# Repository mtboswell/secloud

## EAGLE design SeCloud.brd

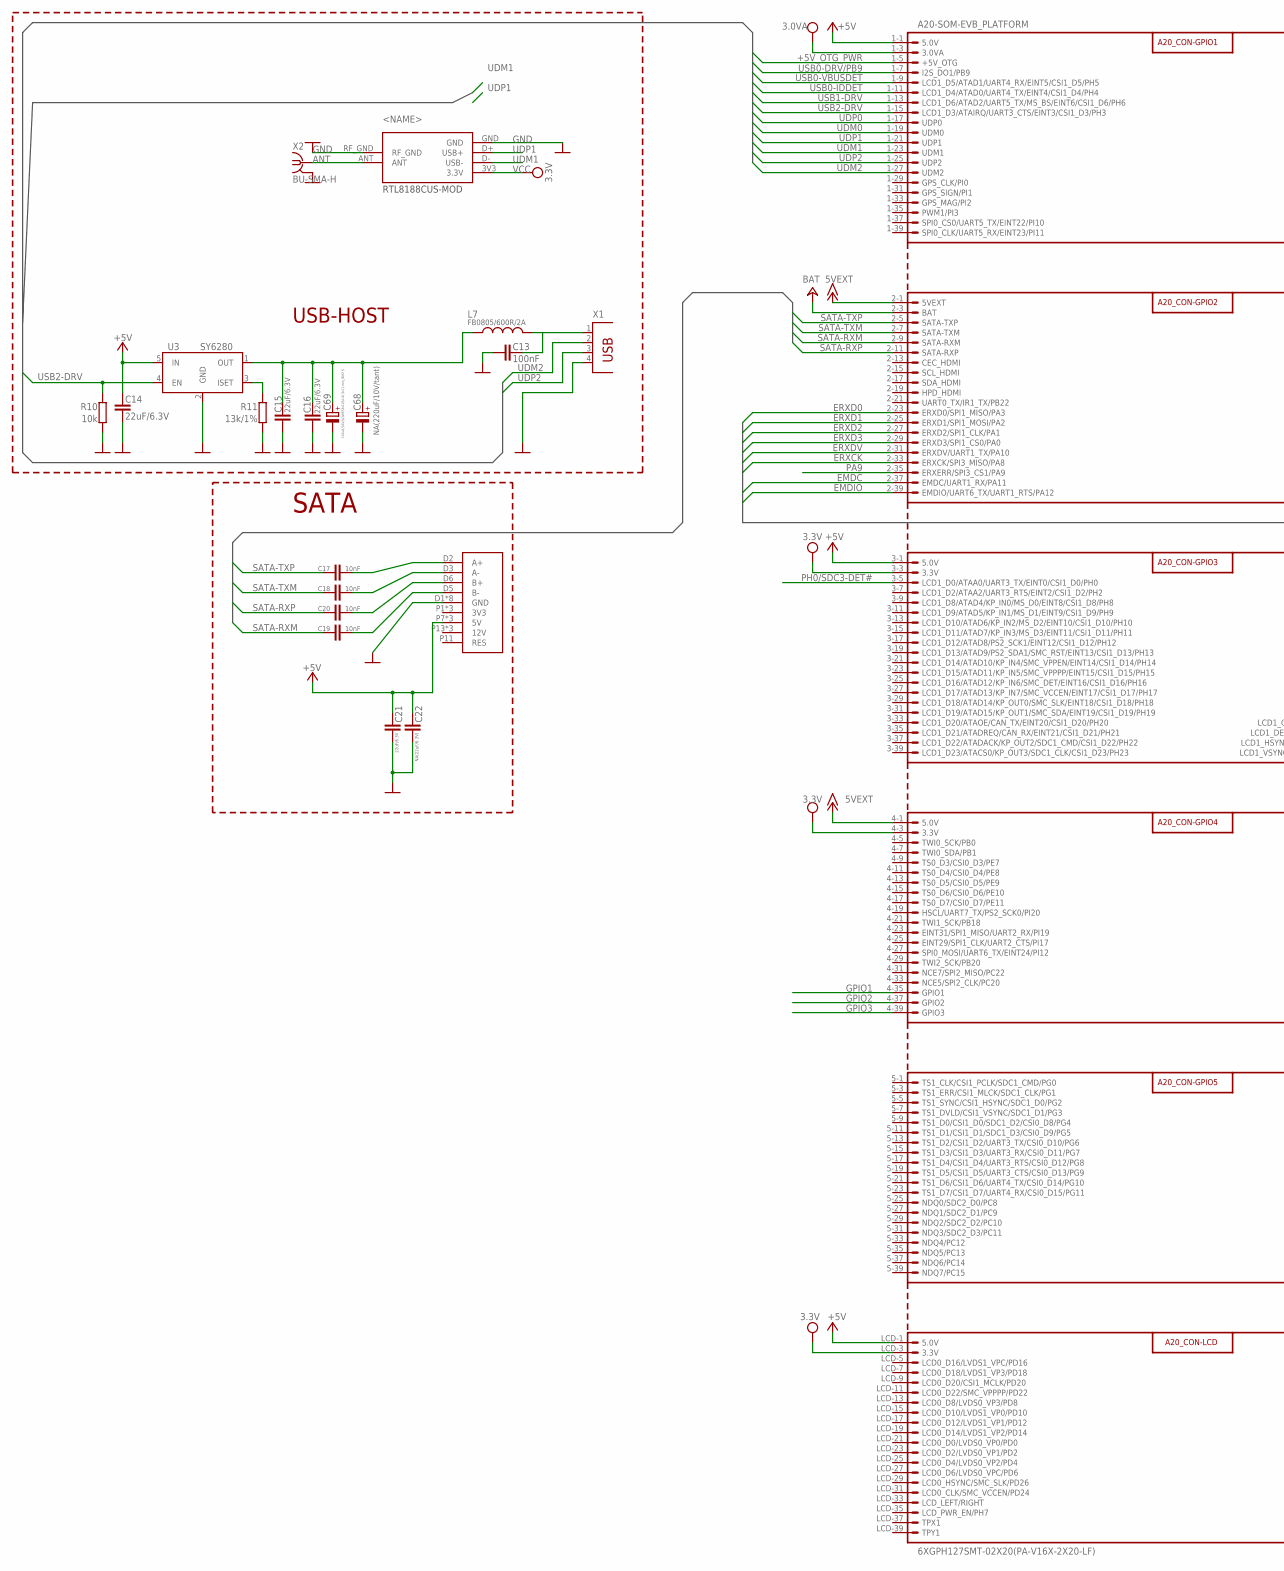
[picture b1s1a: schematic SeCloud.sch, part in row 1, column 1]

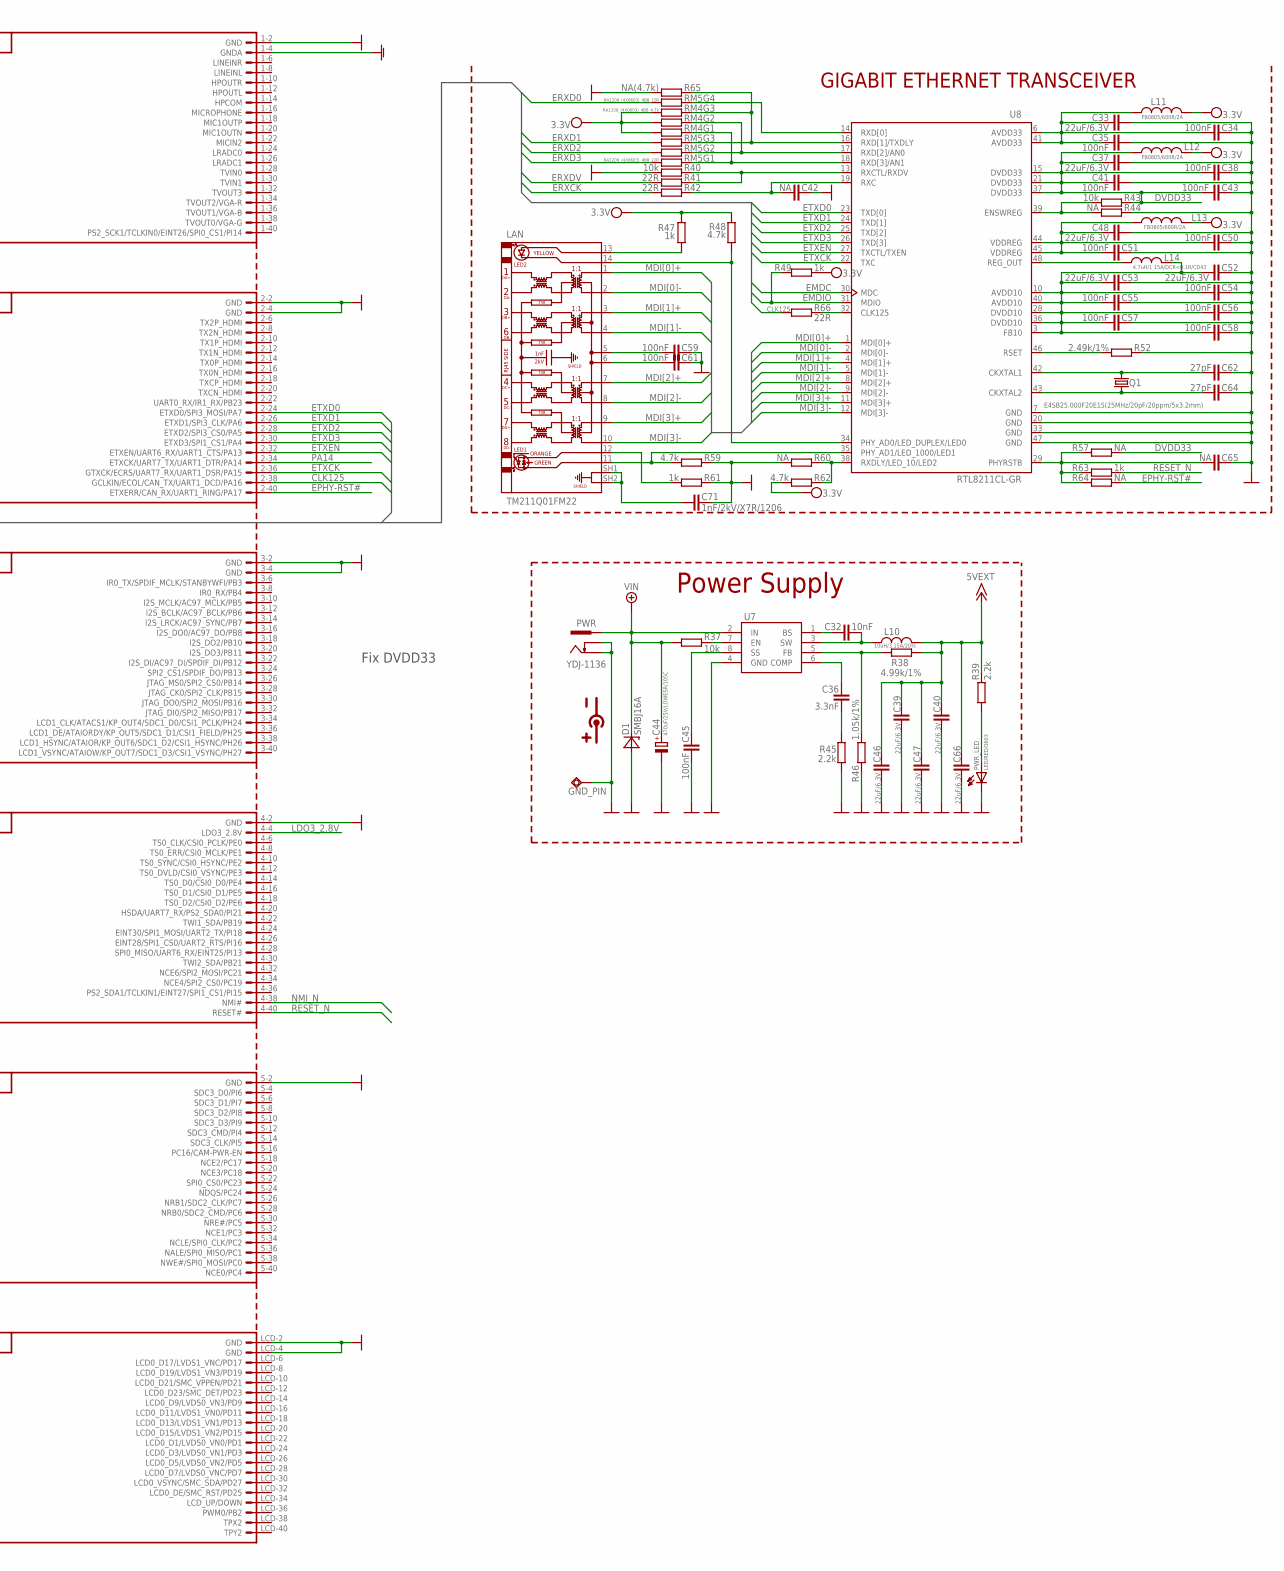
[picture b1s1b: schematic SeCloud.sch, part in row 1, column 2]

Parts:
A20-SOM-EVB_PLATFORM: 6XGPH127SMT-02X20(PA-V16X-2X20-LF); A20-SOM-EVB
C13, C34, C35, C38, C41, C43, C45, C50, C51, C54, C55, C56, C57, C58, C59, C61: 100nF; C0603_DWS
C14, C15, C16, C21, C33, C37, C39, C40, C46, C47, C48, C52, C53, C66: 22uF/6.3V; C0603_DWS
C17, C18, C19, C20, C32: 10nF; C0603_DWS
C22: NA(22uF/6.3V); C0603_DWS
C36: 3.3nF; C0603_DWS
C42, C65: NA; C0603_DWS
C44: 470uF/25V/LOWESR/105C; E3,5-8
C62, C64: 27pF; C0603_DWS
C68: NA(220uF/10V/tant); CT7343
C69: 100uF/16V/LOWESR/105C/6.3x11mm_RM2.5; E2,5-6,3
C71: 1nF/2kV/X7R/1206; C1206_5MILS_WS_ISO
D1: SMBJ16A; DO214AA
GND_PIN: TESTPAD3; TEST_PAD40/70/SQUARE
L7, L11, L12, L13: FB0805/600R/2A; L0805_5MIL_DWS
L10: 10uH/3.15A/20%; 8X7MM_3131
L14: 4.7uH/1.15A/DCR<0.1R/CD43; CD42(43)
LAN: TM211Q01FM22; TM211Q01FM22_SH
PWR: YDJ-1136; PWR_JACK_UNI_MILLING
PWR_LED: LED/RED/0603; LED-0603
Q1: E4SB25.000F20E15(25MHz/20pF/20ppm/5x3.2mm); HCX-4S
R10, R37, R40, R43: 10k; R0603_5MIL_DWS
R11: 13k/1%; R0603_5MIL_DWS
R38: 4.99k/1%; R0603_5MIL_DWS
R39, R45: 2.2k; R0603_5MIL_DWS
R41, R42, R66: 22R; R0603_5MIL_DWS
R44, R57, R60, R64: NA; R0603_5MIL_DWS
R46: 1.05k/1%; R0603_5MIL_DWS
R47, R49, R61, R63: 1k; R0603_5MIL_DWS
R48, R59, R62: 4.7k; R0603_5MIL_DWS
R52: 2.49k/1%; R0603_5MIL_DWS
R65: NA(4.7k); R0603_5MIL_DWS
RM4: RA1206_(4X0603)_4B8_4.7k; R_MATRIX_4
RM5: RA1206_(4X0603)_4B8_22R; R_MATRIX_4
U3: SY6280; SOT23-5
U7: MP1482DS; SOIC8
U8: RTL8211CL-GR; LQFP48
U$1: RTL8188CUS-MOD
U$2: SATA-CON
X1: PN87520
X2: BU-SMA-H

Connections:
+5V: A20-SOM-EVB_PLATFORM.1-1 (5.0V), A20-SOM-EVB_PLATFORM.3-1 (5.0V), A20-SOM-EVB_PLATFORM.LCD-1 (5.0V), C14.1, C21.2, C22.2, U3.5 (IN), U$2.P7 (5V), U$2.P8 (5V), U$2.P9 (5V)
+5V_OTG_PWR: A20-SOM-EVB_PLATFORM.1-5 (+5V_OTG)
+12V: C44.+, D1.C, PWR.+, R37.1, U7.2 (IN)
+15V: A20-SOM-EVB_PLATFORM.2-1 (5VEXT), A20-SOM-EVB_PLATFORM.4-1 (5.0V), C39.1, C40.1, C46.1, C47.1, C66.1, L10.2, R38.2, R39.1
+24V: A20-SOM-EVB_PLATFORM.2-3 (BAT)
ANT: U$1.ANT, X2.1
AVDD33: C33.2, C34.2, C35.2, L11.2, U8.6 (AVDD33), U8.41 (AVDD33)
AVDD/DVDD(1.05V): C52.2, C53.2, C54.2, C55.2, C56.2, C57.2, C58.2, L14.2, U8.3 (FB10), U8.10 (AVDD10), U8.28 (DVDD10), U8.36 (DVDD10), U8.40 (AVDD10)
CLK125: A20-SOM-EVB_PLATFORM.2-38 (GCLKIN/ECOL/CAN_TX/UART1_DCD/PA16), R66.1
DVDD33: C37.2, C38.2, C41.2, C43.2, L12.2, R43.1, R57.1, U8.15 (DVDD33), U8.21 (DVDD33), U8.37 (DVDD33)
EMDC: A20-SOM-EVB_PLATFORM.2-37 (EMDC/UART1_RX/PA11), U8.30 (MDC)
EMDIO: A20-SOM-EVB_PLATFORM.2-39 (EMDIO/UART6_TX/UART1_RTS/PA12), R49.1, U8.31 (MDIO)
EPHY-RST#: A20-SOM-EVB_PLATFORM.2-40 (ETXERR/CAN_RX/UART1_RING/PA17), R64.1
ERXCK: A20-SOM-EVB_PLATFORM.2-33 (ERXCK/SPI3_MISO/PA8), R42.2
ERXD0: A20-SOM-EVB_PLATFORM.2-23 (ERXD0/SPI1_MISO/PA3), RM5.4.2 (2)
ERXD1: A20-SOM-EVB_PLATFORM.2-25 (ERXD1/SPI1_MOSI/PA2), RM5.3.2 (2)
ERXD2: A20-SOM-EVB_PLATFORM.2-27 (ERXD2/SPI1_CLK/PA1), RM5.2.2 (2)
ERXD3: A20-SOM-EVB_PLATFORM.2-29 (ERXD3/SPI1_CS0/PA0), RM5.1.2 (2)
ERXDV: A20-SOM-EVB_PLATFORM.2-31 (ERXDV/UART1_TX/PA10), R41.2
ETXCK: A20-SOM-EVB_PLATFORM.2-36 (GTXCK/ECRS/UART7_RX/UART1_DSR/PA15), U8.22 (TXC)
ETXD0: A20-SOM-EVB_PLATFORM.2-24 (ETXD0/SPI3_MOSI/PA7), U8.23 (TXD[0])
ETXD1: A20-SOM-EVB_PLATFORM.2-26 (ETXD1/SPI3_CLK/PA6), U8.24 (TXD[1])
ETXD2: A20-SOM-EVB_PLATFORM.2-28 (ETXD2/SPI3_CS0/PA5), U8.25 (TXD[2])
ETXD3: A20-SOM-EVB_PLATFORM.2-30 (ETXD3/SPI1_CS1/PA4), U8.26 (TXD[3])
ETXEN: A20-SOM-EVB_PLATFORM.2-32 (ETXEN/UART6_RX/UART1_CTS/PA13), U8.27 (TXCTL/TXEN)
GND: A20-SOM-EVB_PLATFORM.1-2 (GND), A20-SOM-EVB_PLATFORM.2-2 (GND), A20-SOM-EVB_PLATFORM.2-4 (GND), A20-SOM-EVB_PLATFORM.3-2 (GND), A20-SOM-EVB_PLATFORM.3-4 (GND), A20-SOM-EVB_PLATFORM.4-2 (GND), A20-SOM-EVB_PLATFORM.5-2 (GND), A20-SOM-EVB_PLATFORM.LCD-2 (GND), A20-SOM-EVB_PLATFORM.LCD-4 (GND), C13.2, C14.2, C15.2, C16.2, C21.1, C22.1, C33.1, C34.1, C35.1, C37.1, C38.1, C39.2, C40.2, C41.1, C42.2, C43.1, C44.-, C45.2, C46.2, C47.2, C48.1, C50.1, C51.1, C52.1, C53.1, C54.1, C55.1, C56.1, C57.1, C58.1, C59.1, C61.1, C62.1, C64.1, C65.1, C66.2, C68.-, C69.-, C71.1, D1.A, GND_PIN.P$1, PWR.-, PWR.--, PWR_LED.C, R10.1, R11.1, R40.2, R44.1, R45.2, R46.2, R52.1, R59.1, R60.2, R61.1, R65.2, U3.2 (GND), U7.4 (GND), U8.7 (GND), U8.20 (GND), U8.33 (GND), U8.47 (GND), U$1.GND, U$1.RF_GND, U$2.D1 (GND), U$2.D4 (GND), U$2.D7 (GND), U$2.P4 (GND), U$2.P5 (GND), U$2.P6 (GND), U$2.P10 (GND), U$2.P12 (GND), X1.4, X2.2, X2.3 (2), X2.4 (2), X2.5 (2)
GNDA: A20-SOM-EVB_PLATFORM.1-4 (GNDA)
GPIO1: A20-SOM-EVB_PLATFORM.4-35 (GPIO1)
GPIO2: A20-SOM-EVB_PLATFORM.4-37 (GPIO2)
GPIO3: A20-SOM-EVB_PLATFORM.4-39 (GPIO3)
LDO3_2.8V: A20-SOM-EVB_PLATFORM.4-4 (LDO3_2.8V)
MDI[0]+: LAN.1, U8.1 (MDI[0]+)
MDI[0]-: LAN.2, U8.2 (MDI[0]-)
MDI[1]+: LAN.3, U8.4 (MDI[1]+)
MDI[1]-: LAN.4, U8.5 (MDI[1]-)
MDI[2]+: LAN.7, U8.8 (MDI[2]+)
MDI[2]-: LAN.8, U8.9 (MDI[2]-)
MDI[3]+: LAN.9, U8.11 (MDI[3]+)
MDI[3]-: LAN.10, U8.12 (MDI[3]-)
unnamed: C45.1, U7.8 (SS)
unnamed: R37.2, U7.7 (EN)
unnamed: C32.1, U7.1 (BS)
unnamed: C32.2, L10.1, U7.3 (SW)
unnamed: C36.1, U7.6 (COMP)
unnamed: C36.2, R45.1
unnamed: C71.2, LAN.SH1, LAN.SH2
unnamed: R52.2, U8.46 (RSET)
unnamed: C62.2, Q1.2, U8.42 (CKXTAL1)
unnamed: C64.2, Q1.1, U8.43 (CKXTAL2)
unnamed: L14.1, U8.48 (REG_OUT)
unnamed: C59.2, LAN.5
unnamed: C65.2, R57.2, R63.2, R64.2, U8.29 (PHYRSTB)
unnamed: C61.2, LAN.6
unnamed: R60.1, R62.1, U8.38 (RXDLY/LED_10/LED2)
unnamed: LAN.12, R61.2
unnamed: LAN.11, R59.2, U8.35 (PHY_AD1/LED_1000/LED1)
unnamed: R43.2, R44.2, U8.39 (ENSWREG)
unnamed: LAN.13, R47.2
unnamed: C42.1, R42.1, U8.19 (RXC)
unnamed: R66.2, U8.32 (CLK125)
unnamed: R40.1, R41.1, U8.13 (RXCTL/RXDV)
unnamed: RM5.4.1 (1), U8.14 (RXD[0])
unnamed: R65.1, RM4.3.1 (1), RM5.3.1 (1), U8.16 (RXD[1]/TXDLY)
unnamed: RM4.2.1 (1), RM5.2.1 (1), U8.17 (RXD[2]/AN0)
unnamed: RM4.1.1 (1), RM5.1.1 (1), U8.18 (RXD[3]/AN1)
unnamed: LAN.14, R48.1, U8.34 (PHY_AD0/LED_DUPLEX/LED0)
unnamed: R38.1, R46.1, U7.5 (FB)
unnamed: C17.2, U$2.D2 (A+)
unnamed: C18.2, U$2.D3 (A-)
unnamed: C19.2, U$2.D5 (B-)
unnamed: C20.2, U$2.D6 (B+)
unnamed: PWR_LED.A, R39.2
unnamed: R11.2, U3.3 (ISET)
unnamed: C13.1, L7.2, X1.1
unnamed: C15.1, C16.1, C68.+, C69.+, L7.1, U3.1 (OUT)
NMI_N: A20-SOM-EVB_PLATFORM.4-38 (NMI#)
PA9: A20-SOM-EVB_PLATFORM.2-35 (ERXERR/SPI3_CS1/PA9)
PA14: A20-SOM-EVB_PLATFORM.2-34 (ETXCK/UART7_TX/UART1_DTR/PA14)
PH0/SDC3-DET#: A20-SOM-EVB_PLATFORM.3-5 (LCD1_D0/ATAA0/UART3_TX/EINT0/CSI1_D0/PH0)
RESET_N: A20-SOM-EVB_PLATFORM.4-40 (RESET#), R63.1
SATA-RXM: A20-SOM-EVB_PLATFORM.2-9 (SATA-RXM), C19.1
SATA-RXP: A20-SOM-EVB_PLATFORM.2-11 (SATA-RXP), C20.1
SATA-TXM: A20-SOM-EVB_PLATFORM.2-7 (SATA-TXM), C18.1
SATA-TXP: A20-SOM-EVB_PLATFORM.2-5 (SATA-TXP), C17.1
UDM0: A20-SOM-EVB_PLATFORM.1-19 (UDM0)
UDM1: A20-SOM-EVB_PLATFORM.1-23 (UDM1), U$1.D- (USB-)
UDM2: A20-SOM-EVB_PLATFORM.1-27 (UDM2), X1.2
UDP0: A20-SOM-EVB_PLATFORM.1-17 (UDP0)
UDP1: A20-SOM-EVB_PLATFORM.1-21 (UDP1), U$1.D+ (USB+)
UDP2: A20-SOM-EVB_PLATFORM.1-25 (UDP2), X1.3
USB0-DRV/PB9: A20-SOM-EVB_PLATFORM.1-7 (I2S_DO1/PB9)
USB0-IDDET: A20-SOM-EVB_PLATFORM.1-11 (LCD1_D4/ATAD0/UART4_TX/EINT4/CSI1_D4/PH4)
USB0-VBUSDET: A20-SOM-EVB_PLATFORM.1-9 (LCD1_D5/ATAD1/UART4_RX/EINT5/CSI1_D5/PH5)
USB1-DRV: A20-SOM-EVB_PLATFORM.1-13 (LCD1_D6/ATAD2/UART5_TX/MS_BS/EINT6/CSI1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)
USB2-DRV: A20-SOM-EVB_PLATFORM.1-15 (LCD1_D3/ATAIRQ/UART3_CTS/EINT3/CSI1_D3/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), R10.2, U3.4 (EN)
VCC: A20-SOM-EVB_PLATFORM.3-3 (3.3V), A20-SOM-EVB_PLATFORM.4-3 (3.3V), A20-SOM-EVB_PLATFORM.LCD-3 (3.3V), L11.1, L12.1, L13.1, R47.1, R48.2, R49.2, R62.2, RM4.1.2 (2), RM4.2.2 (2), RM4.3.2 (2), U$1.3V3 (3.3V)
VDDREG: C48.2, C50.2, C51.2, L13.2, U8.44 (VDDREG), U8.45 (VDDREG)
VPP: A20-SOM-EVB_PLATFORM.1-3 (3.0VA)

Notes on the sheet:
USB-HOST
Power Supply
GIGABIT ETHERNET TRANSCEIVER
SATA
Fix DVDD33

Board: 2 copper layers, 94 parts (4 on the bottom side), 80 nets, no tracks yet.

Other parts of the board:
U$5: LOGO-OPENHARDWARE_8X8
U$11: RECYCLE_BIN1/8

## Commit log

2015-04-04 Adding Eagle PCB files
2015-04-05 Added lbr, RTL8188 module, and SATA connector;
